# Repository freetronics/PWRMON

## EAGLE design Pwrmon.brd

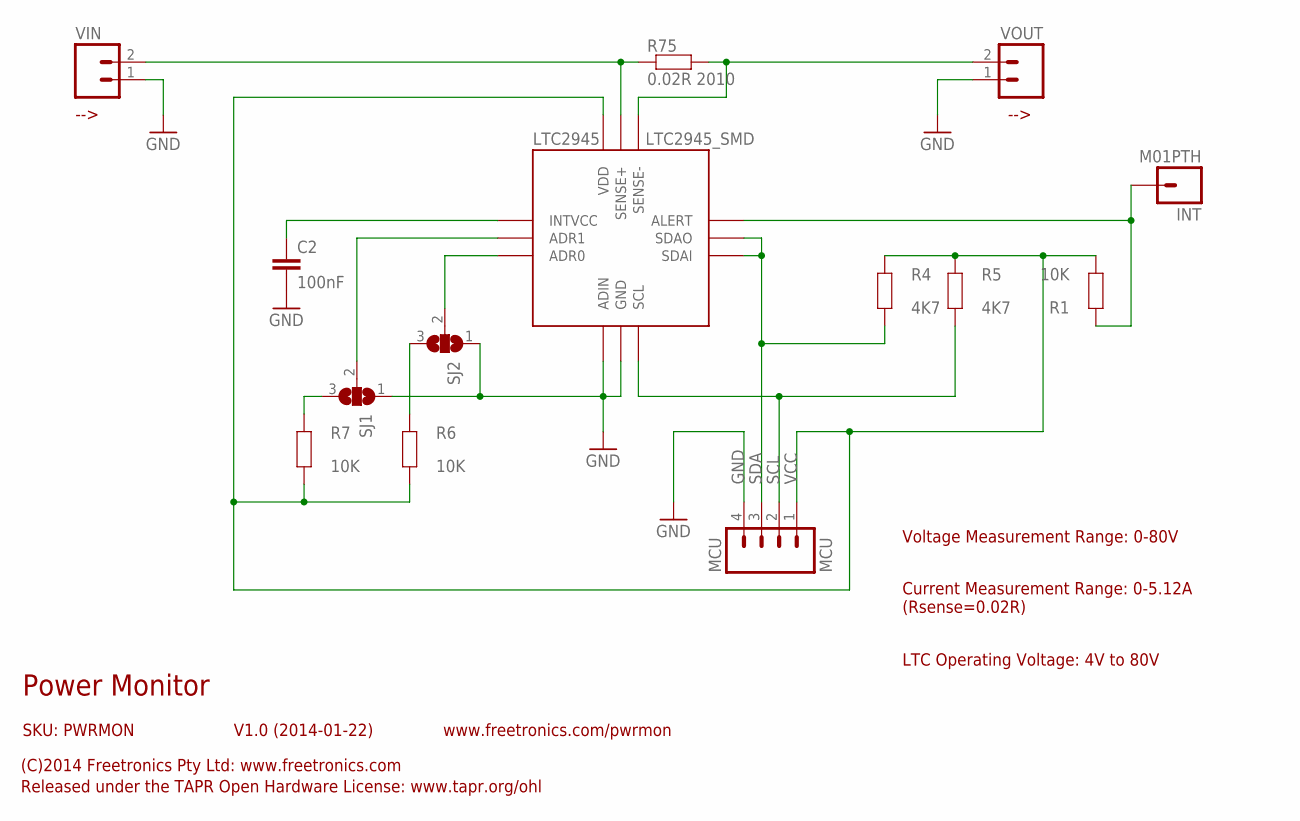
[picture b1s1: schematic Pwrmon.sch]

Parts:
C2: 100nF; 0603
INT: M01PTH; 1X01
LTC2945: LTC2945_SMD; QFN-12
MCU: MCU; 1X04
R1, R6, R7: 10K; 0603
R4, R5: 4K7; 0603
R75: 0.02R 2010; R2010
SJ1, SJ2: SJ2W; SJ_2
VIN: M02PTH; 1X02
VOUT: M02PTH; 1X02

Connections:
GND: C2.2, LTC2945.4 (ADIN), LTC2945.5 (GND), MCU.4, SJ1.1, SJ2.1, VIN.1, VOUT.1
unnamed: LTC2945.11 (SENSE+), R75.1, VIN.2
unnamed: LTC2945.10 (SENSE-), R75.2, VOUT.2
unnamed: LTC2945.2 (ADR1), SJ1.2
unnamed: INT.1, LTC2945.9 (ALERT), R1.2
unnamed: C2.1, LTC2945.1 (INTVCC)
unnamed: LTC2945.3 (ADR0), SJ2.2
unnamed: R7.2, SJ1.3
unnamed: R6.2, SJ2.3
SCL: LTC2945.6 (SCL), MCU.2, R5.1
SDA: LTC2945.7 (SDAI), LTC2945.8 (SDAO), MCU.3, R4.1
VCC: LTC2945.12 (VDD), MCU.1, R1.1, R4.2, R5.2, R6.1, R7.1

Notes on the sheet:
Power Monitor
V1.0 (2014-01-22)
SKU: PWRMON
(C)2014 Freetronics Pty Ltd: www.freetronics.com
Released under the TAPR Open Hardware License: www.tapr.org/ohl
www.freetronics.com/pwrmon
LTC Operating Voltage: 4V to 80V
-->
Voltage Measurement Range: 0-80V
Current Measurement Range: 0-5.12A (Rsense=0.02R)

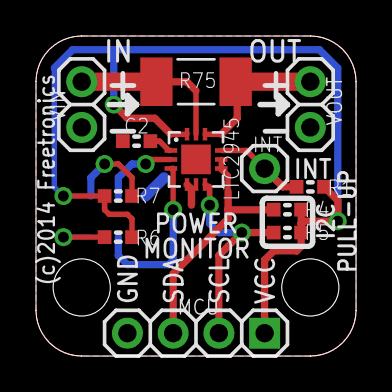
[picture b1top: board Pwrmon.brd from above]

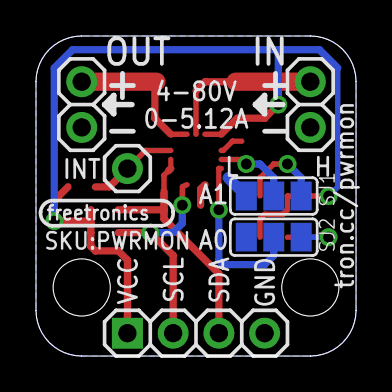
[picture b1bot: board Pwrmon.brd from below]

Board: 2 copper layers, 17.8 x 17.8 mm, 14 parts (2 on the bottom side), 12 nets.

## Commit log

2014-01-21 v1.0 Initial project
2014-01-23 Current range corrected and new labels included.
2014-02-18 Recovered conflicted files from failed merge

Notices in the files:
parts and their libraries:
freetronics-original: Licensing: CC v3.0 Share-Alike You are welcome to use this library for commercial purposes.
